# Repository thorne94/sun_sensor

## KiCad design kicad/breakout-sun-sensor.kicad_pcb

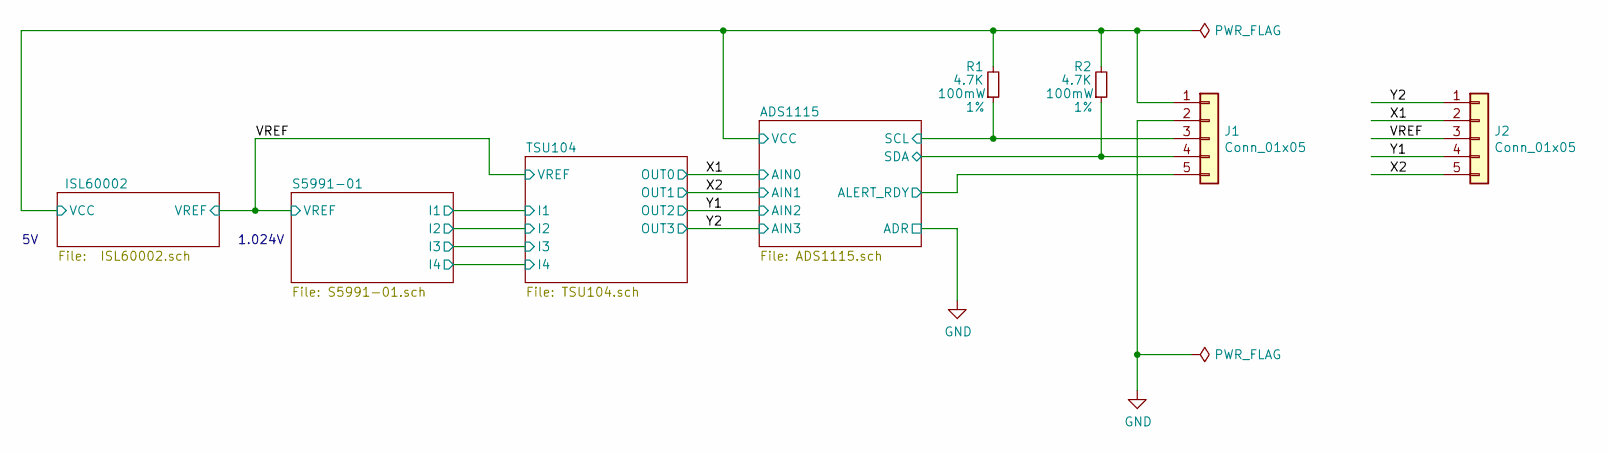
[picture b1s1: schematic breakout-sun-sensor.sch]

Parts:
J1, J2: Conn_01x05; PinHeader_1x05_P2.54mm_Vertical
R1, R2: 4.7K; R_0603_1608Metric; Tolerance 1%

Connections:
/ ISL60002/VCC: J1.1, R1.2, R2.2; also elsewhere on the board
/ADS1115/ALERT_RDY: J1.5; also elsewhere on the board
/ADS1115/SCL: J1.3, R1.1; also elsewhere on the board
/ADS1115/SDA: J1.4, R2.1; also elsewhere on the board
/VREF: J2.3; also elsewhere on the board
/X1: J2.2; also elsewhere on the board
/X2: J2.5; also elsewhere on the board
/Y1: J2.4; also elsewhere on the board
/Y2: J2.1; also elsewhere on the board
GND: J1.2; also elsewhere on the board

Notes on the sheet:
1.024V

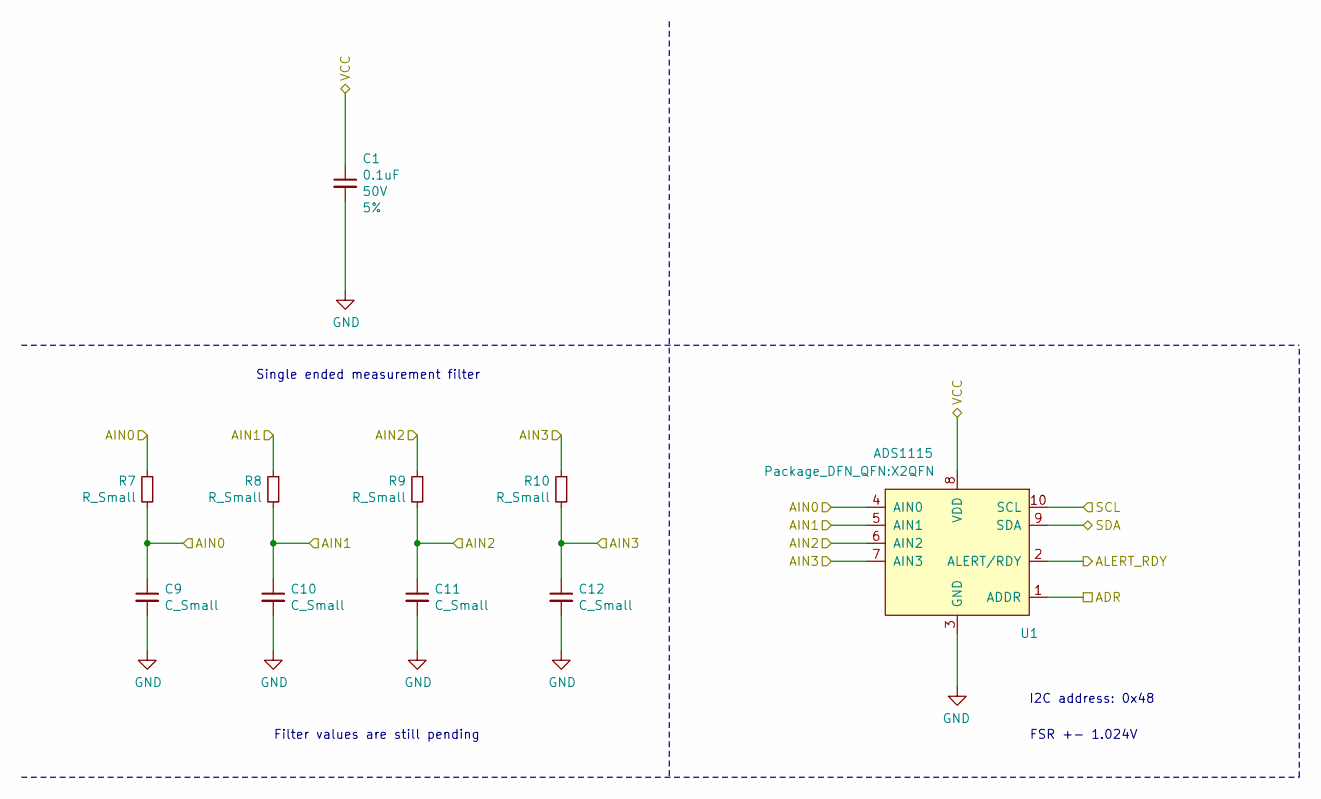
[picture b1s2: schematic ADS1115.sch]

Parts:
C1: 0.1uF; C_0603_1608Metric; Voltage 50V; Tolerance 5%
C9, C10, C11, C12: C_Small; C_0603_1608Metric
R7, R8, R9, R10: R_Small; R_0603_1608Metric
U1: ADS1115; X2QFN

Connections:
/ ISL60002/VCC: C1.1, U1.8 (VDD); also elsewhere on the board
/ADS1115/ALERT_RDY: U1.2 (ALERT/RDY); also elsewhere on the board
/ADS1115/SCL: U1.10 (SCL); also elsewhere on the board
/ADS1115/SDA: U1.9 (SDA); also elsewhere on the board
/X1: C9.1, R7.1, R7.2, U1.4 (AIN0); also elsewhere on the board
/X2: C10.1, R8.1, R8.2, U1.5 (AIN1); also elsewhere on the board
/Y1: C11.1, R9.1, R9.2, U1.6 (AIN2); also elsewhere on the board
/Y2: C12.1, R10.1, R10.2, U1.7 (AIN3); also elsewhere on the board
GND: C1.2, C9.2, C10.2, C11.2, C12.2, U1.1 (ADDR), U1.3 (GND); also elsewhere on the board

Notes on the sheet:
I2C address: 0x48
Single ended measurement filter
Filter values are still pending
FSR +- 1.024V

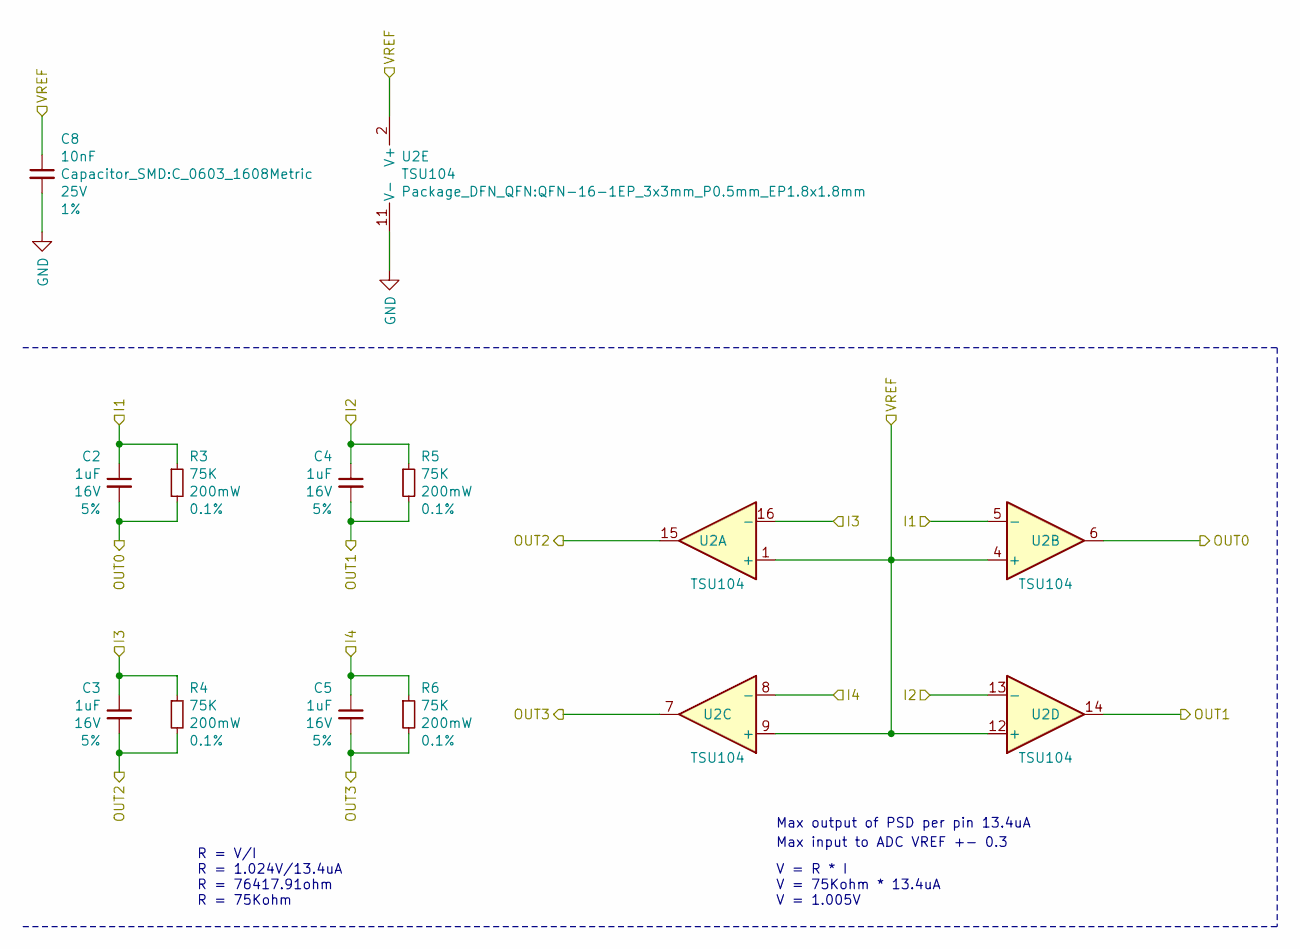
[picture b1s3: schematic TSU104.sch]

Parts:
C2, C3, C4, C5: 1uF; C_0603_1608Metric; Voltage 16V; Tolerance 5%
C8: 10nF; C_0603_1608Metric; Voltage 25V; Tolerance 1%
R3, R4, R5, R6: 75K; R_0603_1608Metric; Tolerance 0.1%
U2: TSU104; QFN-16-1EP_3x3mm_P0.5mm_EP1.8x1.8mm

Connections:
/S5991-01/I1: C2.1, R3.1, U2.5 (-); also elsewhere on the board
/S5991-01/I2: C4.1, R5.1, U2.13 (-); also elsewhere on the board
/S5991-01/I3: C3.1, R4.1, U2.16 (-); also elsewhere on the board
/S5991-01/I4: C5.1, R6.1, U2.8 (-); also elsewhere on the board
/VREF: C8.1, U2.1 (+), U2.2 (V+), U2.4 (+), U2.9 (+), U2.12 (+); also elsewhere on the board
/X1: C2.2, R3.2, U2.6; also elsewhere on the board
/X2: C4.2, R5.2, U2.14; also elsewhere on the board
/Y1: C3.2, R4.2, U2.15; also elsewhere on the board
/Y2: C5.2, R6.2, U2.7; also elsewhere on the board
GND: C8.2, U2.11 (V-); also elsewhere on the board

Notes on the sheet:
Max input to ADC VREF +- 0.3
Max output of PSD per pin 13.4uA
R = V/I R = 1.024V/13.4uA R = 76417.91ohm R = 75Kohm
V = R * I V = 75Kohm * 13.4uA V = 1.005V

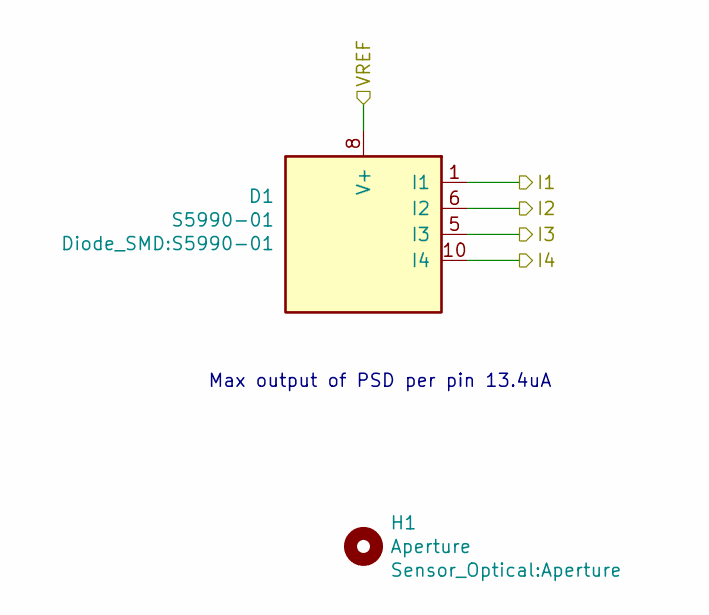
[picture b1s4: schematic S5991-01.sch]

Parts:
D1: S5990-01
H1: Aperture

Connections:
/S5991-01/I1: D1.1 (I1); also elsewhere on the board
/S5991-01/I2: D1.6 (I2); also elsewhere on the board
/S5991-01/I3: D1.5 (I3); also elsewhere on the board
/S5991-01/I4: D1.10 (I4); also elsewhere on the board
/VREF: D1.8 (V+); also elsewhere on the board

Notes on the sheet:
Max output of PSD per pin 13.4uA

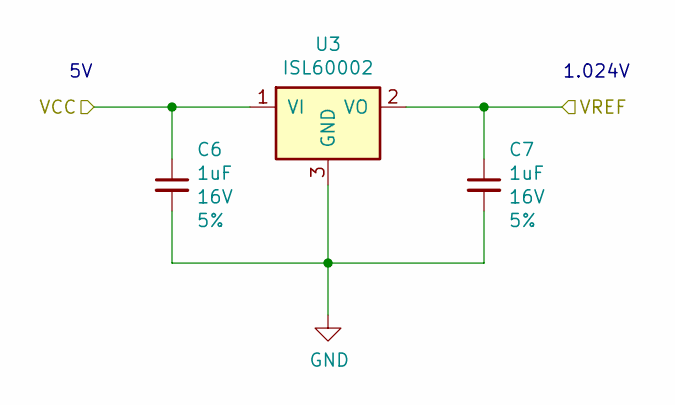
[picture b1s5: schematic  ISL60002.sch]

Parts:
C6, C7: 1uF; C_0603_1608Metric; Voltage 16V; Tolerance 5%
U3: ISL60002; SOT-23

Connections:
/ ISL60002/VCC: C6.1, U3.1 (VI); also elsewhere on the board
/VREF: C7.1, U3.2 (VO); also elsewhere on the board
GND: C6.2, C7.2, U3.3 (GND); also elsewhere on the board

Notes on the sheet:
1.024V

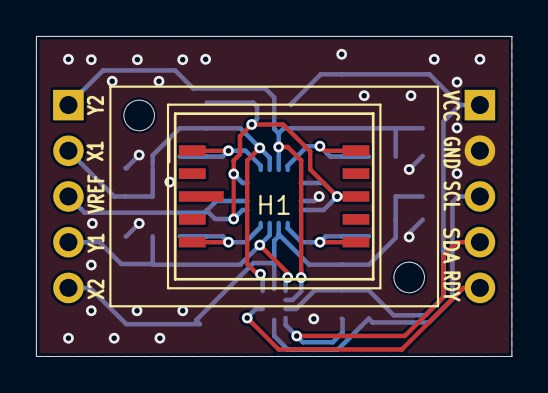
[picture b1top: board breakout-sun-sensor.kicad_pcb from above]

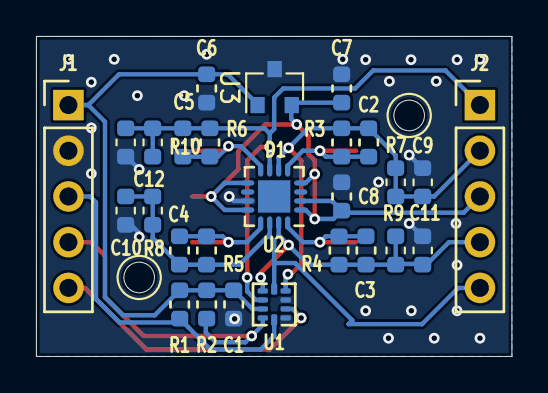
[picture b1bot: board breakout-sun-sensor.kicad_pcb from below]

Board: 2 copper layers, 26.4 x 17.8 mm, 29 parts (27 on the bottom side), 14 nets.

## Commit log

2022-02-21 Initial file upload
